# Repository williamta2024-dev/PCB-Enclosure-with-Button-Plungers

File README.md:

# PCB Enclosure Function
This PCB Enclosure function is each button plunger commands what the LED does with each light connected to one button.
## 3D Design
The 3D design was built in Autodesk Fusion and consist of a simple design that gets the job done.
There is 3 holes for the LEDs with 3 button plungers and a hole that opens to the OLED screen.

## Why I decided to make this?
I decided to make this because it is simple and works on skills that I am not great at yet. I got a lot of
experience from doing the 3D design and learned more of Kicad and Fusion.

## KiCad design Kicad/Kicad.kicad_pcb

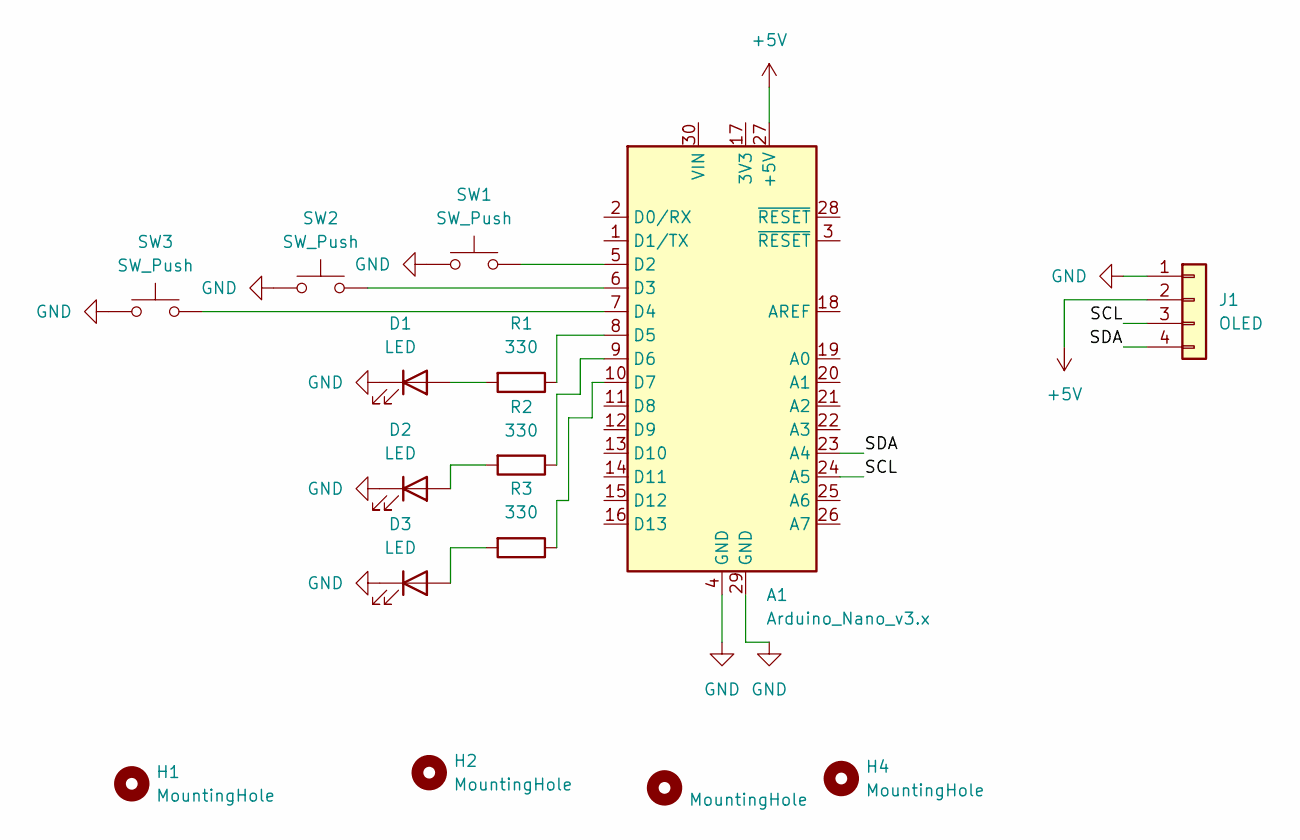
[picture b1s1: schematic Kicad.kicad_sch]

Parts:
A1: Arduino_Nano_v3.x; Arduino_Nano
D1, D2, D3: LED; LED_D5.0mm
H1, H2, H3, H4: MountingHole; MountingHole_3.2mm_M3
J1: OLED; Adafruit_SSD1306
R1, R2, R3: 330; R_Axial_DIN0207_L6.3mm_D2.5mm_P7.62mm_Horizontal
SW1, SW2, SW3: SW_Push; SW_PUSH_6mm

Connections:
+5V: A1.27 (+5V), J1.2
/SCL: A1.24 (A5), J1.3
/SDA: A1.23 (A4), J1.4
GND: A1.4 (GND), A1.29 (GND), D1.1 (K), D2.1 (K), D3.1 (K), J1.1, SW1.1, SW2.1, SW3.1
unnamed: A1.5 (D2), SW1.2
unnamed: A1.6 (D3), SW2.2
unnamed: A1.7 (D4), SW3.2
unnamed: A1.8 (D5), R1.1
unnamed: A1.9 (D6), R2.1
unnamed: A1.10 (D7), R3.1
unnamed: D1.2 (A), R1.2
unnamed: D2.2 (A), R2.2
unnamed: D3.2 (A), R3.2

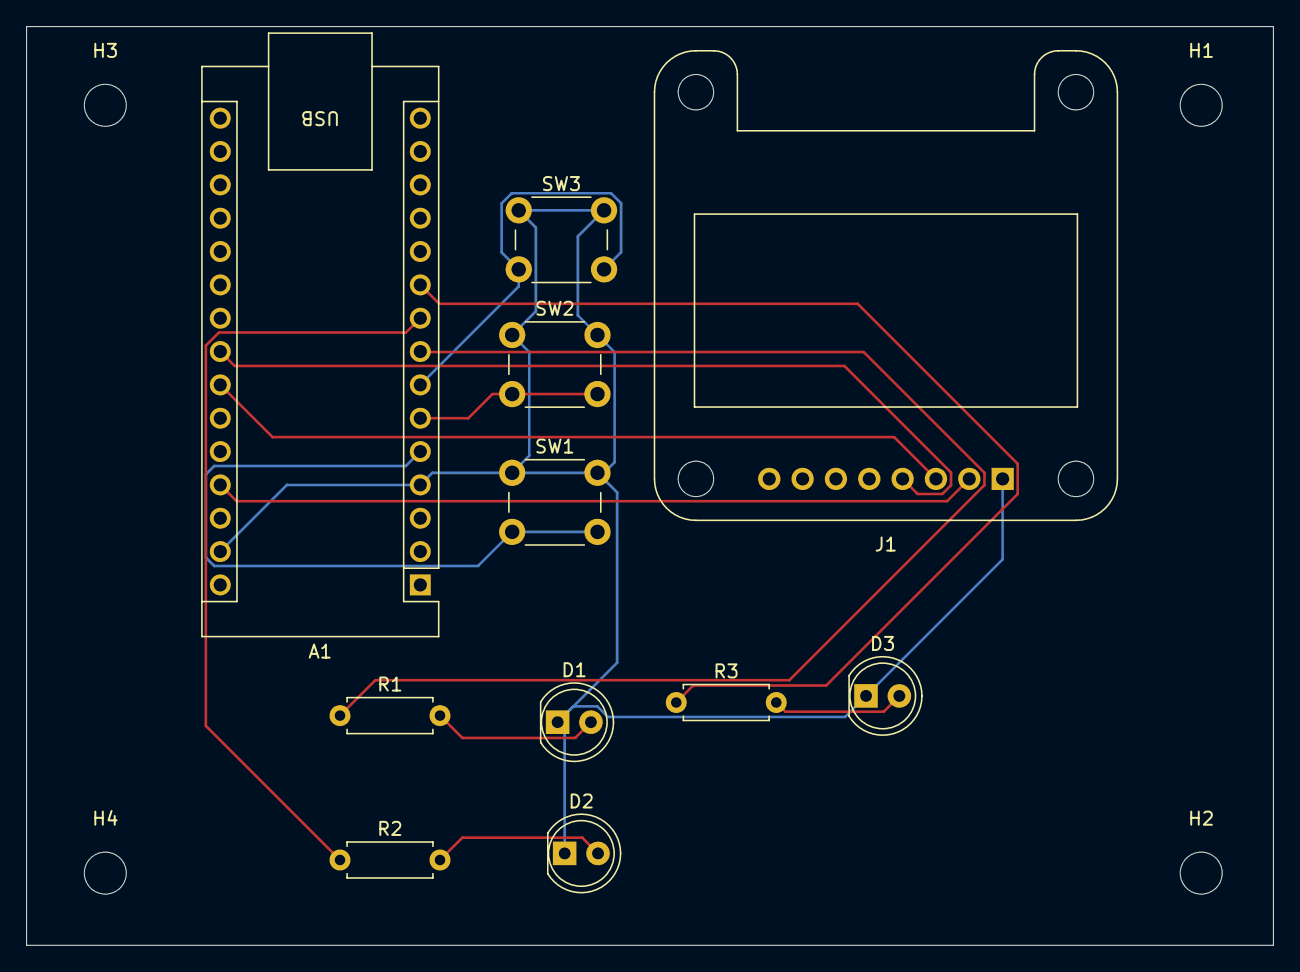
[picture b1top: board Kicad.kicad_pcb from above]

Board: 2 copper layers, 95.0 x 70.0 mm, 15 parts (0 on the bottom side), 13 nets.
